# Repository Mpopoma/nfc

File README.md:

# Happy Bubbles - Wifi NFC Device

This device is in the "Happy Bubbles" series of open hardware and open source IoT and home-automation devices. The Wifi NFC device is easy to use, easy to make yourself, and cheap. 

Its purpose is to send NFC/RFID tags that you touch to it to an HTTP URL on whatever server you'd like.

What you need to build it:
 * a NodeMCU ESP8266 development kit - [buy one here](http://amzn.to/1S03qNE)
 * an RC522 RFID module - [buy one here](http://amzn.to/1U1rVxE)
 * (optional) a WS2812B RGB LED

## How to set it up

#### 0. Initial flashing

Easiest is to download the  release and use your favorite ESP8266 flashing tool to flash the bootloader, the firmware, and blank settings. Detailed instructions are provided in the release notes, thanks tve!

#### 1. Wire it up 
| RC522 NFC pin   |      NodeMCU pin      |  ESP8266 GPIO |
|----------|:-------------:|------:|
| SDA | D8 | GPIO 15 |
| SCK | D5 | GPIO 14 |
| MOSI | D7 | GPIO 13 |
| MISO | D6 | GPIO 12 |
| IRQ | Not connected| Not connected |
| GND | Ground / GND | Ground |
| RST | D4 | GPIO 2 |
| 3.3V | 3.3V / VCC | VCC |

If there is interest, I can create a PCB for you guys to make this easier. Let me know if anyone would like these and I could put them up for sale.

#### 2. Optional WS2812B LED

An RGB LED is useful as a status indicator to tell you when you're in config-mode, when a tag is hit, and the server response can even change its colour!

| WS2812 pin   |      NodeMCU pin      |  ESP8266 GPIO |
|----------|:-------------:|------:|
| GND | GND | GND |
| Data-In | D1 | GPIO 5 |
| 5V Power | VIN | not applicable |

#### 3. Powering it up
Just insert a microUSB cable in the NodeMCU! When it boots up, its red LED should be lit. If you have a WS2812b hooked up, it will glow orange.

If it doesn't, try holding the "FLASH: button on the nodeMCU board held down for about 10 seconds. Holding the button down lets to change between config mode and RFID-scanning mode. I left these two seperate for security, so that while your device is acting as an RFID scanner, someone can't just connect to its hostname and start messing with your settings.

#### 4. Connect it to your wifi network
1. With the board powered up, the Happy Bubbles NFC device will automatically start an access point you can connect to called "happy-bubbles-nfc". 
2. Connect to this access point with your computer
3. Open a browser and visit http://192.168.4.1/
4. You'll now be at the Happy Bubbles config screen! You can change the hostname of the device here.
5. On the left side with the navigation bar, go to "WiFi Setup". It will populate a bunch of wifi access points it can see. Find yours and type in the password. You should see it get an IP address from it, and now you're connected!

#### 5. Make it hit your server
1. From the same  config mode, go to "NFC Setup". In there, you can set some parameters for how the JSON request from the Happy Bubbles device will go to your server.
2. The most important one here is the HTTP URL, this URL will receive a POST request from the device when a tag is scanned.
3. The 'Device ID' is a name you can give this device that will also be included in the JSON. This is useful if you have more than one Happy Bubbles NFC device around and you want to know which one the request is coming from.
4. The 'Device Secret' and 'Device counter' are optional but useful if you want to authenticate the requests to make sure someone isn't spoofing a tag. 

#### 5. Make it run!

Hold down the "FLASH" button on the NodeMCU board for about 10 seconds. The red LED on the NodeMCU should turn on, and if you have an RGB LED hooked up, it will blink purple a few times, fast. It's now reading tags! Every time you touch a tag, the RGB LED will light pink quickly.

## Communication

#### HTTP Request
Every time you touch a tag to the device, it will send an HTTP POST request to the URL you specified in the config. The REQUEST payload will be JSON that looks like this:
```
{
  "device_id": "CONFIG-DEVICE-ID", 
  "tag_uid": "THE-TAGS-UUID", 
  "counter": 3, 
  "hash": "7cac4442e6caf834ce20a359ff7ee9ff34525691"
}
```

The "device_id" is the "Device ID" you specified in the config. The "tag_uuid" is the unique ID of the tag that was detected by the reader. The "counter" and "hash" are optional security authentication parameters described below in the "Optional Authentication" section.

#### HTTP Response
After you touch the tag, the device expects a 200 OK response with a JSON payload. Don't worry about having to send one, it's optional:
```
{
  "r":5,
  "g":250,
  "b":2,
  "delay":2000
}
```

The "r", "g", and "b" are RGB colour values for the optional WS2812B LED. The server could tell the LED to light up a certain way after the request. This way you could give the user some kind of indication of what happened. 

The "delay" is the number of milliseconds to keep the color after a request. If you make it 0, the LED will stay lit that way forever, or until the next reqest...or until you remove power!

## Optional Authentication
The way this authentication works is that the Happy Bubbles NFC device will send a "hash" string in its JSON response. This "hash" is an SHA1-based HMAC, its input is the device-id, the NFC tag-ID, and the counter all concatenated together with no spaces. The 'counter' increments every time your server sends back a 200 OK response. It is used as a 'nonce' to prevent replay attacks on this authentication mechanism.
This string is then SHA1-HMAC'd hashed against the "device secret" from the config menu. You can use this on the backend to ensure no one is spoofing tag-hits, it's optional.

### Credits

This project wouldn't have been possible without my standing on the shoulders of giants such as:
 * [NodeMCU](https://github.com/nodemcu/nodemcu-devkit-v1.0) - The ESP8266-based hardware that this project uses.
 * [esp-link](https://github.com/jeelabs/esp-link) - The firmware for this project is a modified subset of the what JeeLabs' "esp-link" project has built and made this whole thing really nice and easy to work with. 
 * [Espressif](http://espressif.com) - for making the amazing ESP8266 project that enables things like this to even be possible. A wonderful product from a wonderful company.
 * [esphttpd](http://www.esp8266.com/wiki/doku.php?id=esp-httpd) - SpriteTM made an awesome little HTTP webserver for the ESP8266 that powers the config menu of the esp-link and the Happy Bubbles NFC device
 * everyone in the ESP8266 community who shares their code and advice.

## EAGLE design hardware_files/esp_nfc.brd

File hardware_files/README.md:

# Happy Bubbles - Wifi NFC Device

These are the hardware files, in Eagle format, for the Happy Bubbles NFC device.

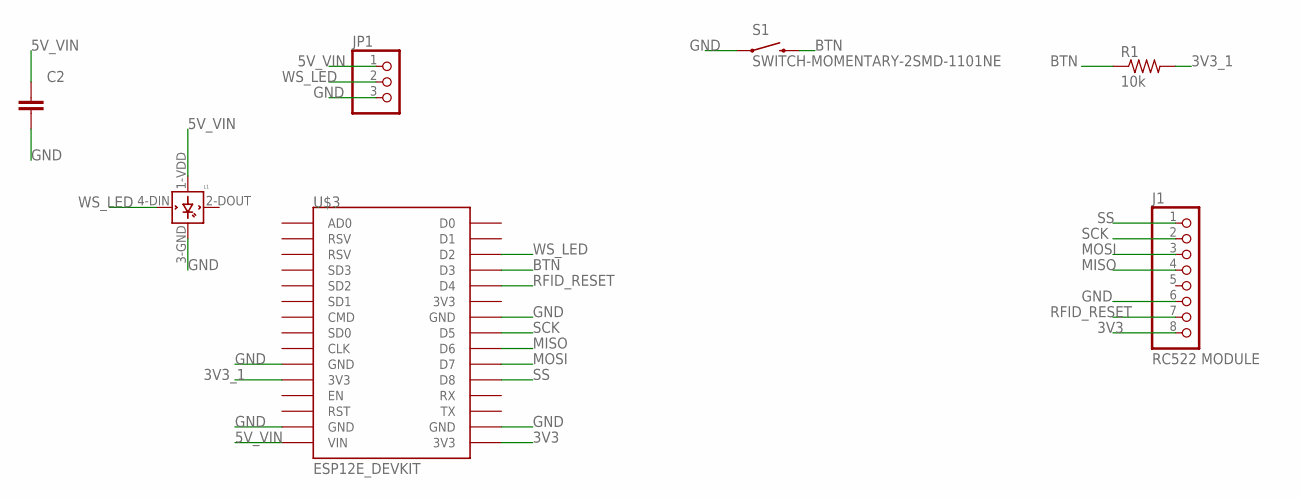
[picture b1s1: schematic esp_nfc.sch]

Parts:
C2: CAPACITOR_NPOL-0603; C603
J1: RC522 MODULE; 1X08-LOCK
JP1: PINHD-1X3; 1X03
L1: WS2812B
R1: 10k; R0603
S1: SWITCH-MOMENTARY-2SMD-1101NE; TACTILE-SWITCH-1101NE
U$3: ESP12E_DEVKIT

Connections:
3V3: J1.8, U$3.3V3@2 (3V3)
3V3_1: R1.2, U$3.3V3@0 (3V3)
5V_VIN: C2.1, JP1.1, L1.1-VDD (VDD), U$3.VIN
BTN: R1.1, S1.2, U$3.D3
GND: C2.2, J1.6, JP1.3, L1.3-GND (GND), S1.1, U$3.GND@0 (GND), U$3.GND@1 (GND), U$3.GND@2 (GND), U$3.GND@3 (GND)
MISO: J1.4, U$3.D6
MOSI: J1.3, U$3.D7
RFID_RESET: J1.7, U$3.D4
SCK: J1.2, U$3.D5
SS: J1.1, U$3.D8
WS_LED: JP1.2, L1.4-DIN (DIN), U$3.D2

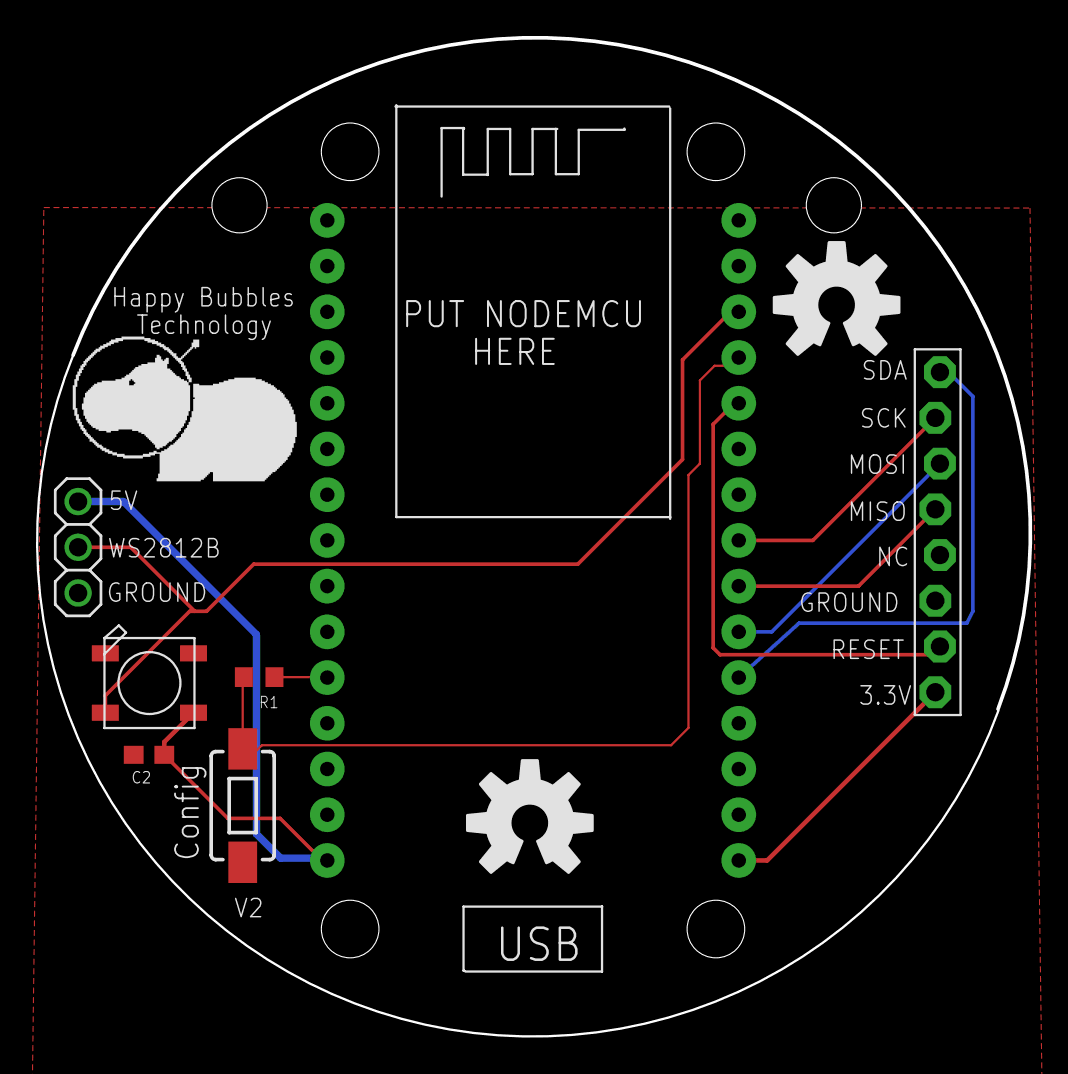
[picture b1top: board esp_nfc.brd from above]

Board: 2 copper layers, 55.2 x 55.5 mm, 11 parts (1 on the bottom side), 11 nets.

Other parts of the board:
U$1: HAPPY_HIPPO_500MIL
U$4, U$6: OSHW-LOGO-L
U$5: HAPPY_HIPPO

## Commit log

2016-03-14 update README with logo
2016-03-15 add EAGLE harware files, schematic and PCB layout
2016-03-15 update hardware readme
2016-12-05 send the payload with the proper content-type as json
2017-10-27 Create CNAME
2017-11-21 Update CNAME

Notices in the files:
parts and their libraries:
SparkFun: Licensing: CC v3.0 Share-Alike You are welcome to use this library for commercial purposes.
SparkFun-Electromechanical: Licensing: Creative Commons ShareAlike 4.0 International - https://creativecommons.org/licenses/by-sa/4.0
